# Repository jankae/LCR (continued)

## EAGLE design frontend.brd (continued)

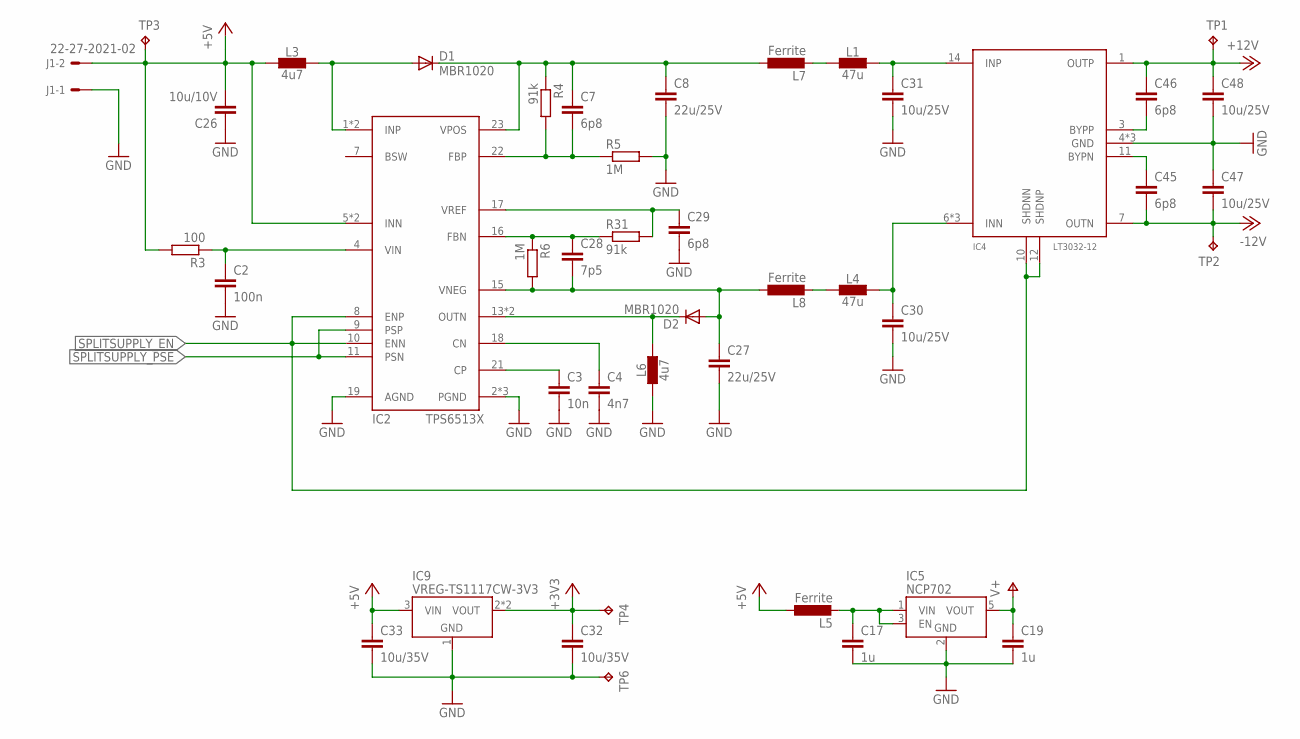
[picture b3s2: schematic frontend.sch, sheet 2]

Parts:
C2: 100n; C0603K
C3: 10n; C0603K
C4: 4n7; C0603K
C7, C29, C45, C46: 6p8; C0603K
C8, C27: 22u/25V; C1206K
C17, C19: 1u; C0603
C26: 10u/10V; C1206K
C28: 7p5; C0603K
C30, C31, C47, C48: 10u/25V; C1206K
C32, C33: 10u/35V; C1206K
D1, D2: MBR1020; SOD123
IC2: TPS6513X; QFN50P400X400X100-25T250N
IC4: LT3032-12; SON50P300X400X80-14N
IC5: NCP702; SOT95P240X110-5
IC9: VREG-TS1117CW-3V3; SOT223
J1: 22-27-2021-02; 6410-02
L1, L4: 47u; L_1212
L3, L6: 4u7; L_1212
L5, L7, L8: Ferrite; R0603
R3: 100; R0603
R4, R31: 91k; R0603
R5, R6: 1M; R0603
TP1, TP2, TP3, TP4, TP6: TPB2,54; B2,54

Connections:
+3V3: C32.1, IC9.2 (VOUT), IC9.4 (VOUT), TP4.TP; also elsewhere on the board
+5V: C26.2, C33.1, IC2.5 (INN), IC2.6 (INN), IC9.3 (VIN), J1.2, L3.1, L5.1, R3.2, TP3.TP; also elsewhere on the board
+12V: C46.1, C48.1, IC4.1 (OUTP), TP1.TP; also elsewhere on the board
-12V: C45.2, C47.2, IC4.7 (OUTN), TP2.TP; also elsewhere on the board
GND: C2.2, C3.2, C4.2, C8.2, C17.2, C19.2, C26.1, C27.2, C29.2, C30.2, C31.2, C32.2, C33.2, C47.1, C48.2, IC2.2 (PGND), IC2.3 (PGND), IC2.19 (AGND), IC2.25 (PGND), IC4.4 (GND), IC4.5 (GND), IC4.EP4 (GND), IC5.2 (GND), IC9.1 (GND), J1.1, L6.1, R5.2, TP6.TP; also elsewhere on the board
unnamed: C17.1, IC5.1 (VIN), IC5.3 (EN), L5.2
unnamed: C2.1, IC2.4 (VIN), R3.1
unnamed: D1.A, IC2.1 (INP), IC2.24 (INP), L3.2
unnamed: C7.1, C8.1, D1.C, IC2.23 (VPOS), L7.1, R4.1
unnamed: D2.C, IC2.13 (OUTN), IC2.14 (OUTN), L6.2
unnamed: C3.1, IC2.21 (CP)
unnamed: C4.1, IC2.18 (CN)
unnamed: C7.2, IC2.22 (FBP), R4.2, R5.1
unnamed: C27.1, C28.2, D2.A, IC2.15 (VNEG), L8.1, R6.2
unnamed: L4.1, L8.2
unnamed: C30.1, IC4.6 (INN), IC4.9 (INN), IC4.EP9 (INN), L4.2
unnamed: C29.1, IC2.17 (VREF), R31.2
unnamed: C28.1, IC2.16 (FBN), R6.1, R31.1
unnamed: L1.1, L7.2
unnamed: C31.1, IC4.14 (INP), L1.2
unnamed: C46.2, IC4.3 (BYPP)
unnamed: C45.1, IC4.11 (BYPN)
SPLITSUPPLY_EN: IC2.8 (ENP), IC2.10 (ENN), IC4.10 (SHDNN), IC4.12 (SHDNP)
SPLITSUPPLY_PSE: IC2.9 (PSP), IC2.11 (PSN)
V+: C19.1, IC5.5 (VOUT); also elsewhere on the board

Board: 4 copper layers, 114 parts (4 on the bottom side), 85 nets, no tracks yet.

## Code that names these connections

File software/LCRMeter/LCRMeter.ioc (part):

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Mcu.Name=STM32F303V(D-E)Tx
Mcu.Package=LQFP100
Mcu.UserName=STM32F303VETx
PA0.GPIOParameters=GPIO_Label
PA0.GPIO_Label=TOUCH_IRQ
PA0.Signal=GPIO_Input
PA1.GPIOParameters=GPIO_Speed,PinState,GPIO_Label
PA1.GPIO_Label=DISP_CS
PA1.GPIO_Speed=GPIO_SPEED_FREQ_HIGH
PA1.PinState=GPIO_PIN_SET
PA1.Signal=GPIO_Output
PA10.Mode=Asynchronous
PA10.Signal=USART1_RX
PA11.Mode=Device
PA11.Signal=USB_DM
PA12.Mode=Device
PA12.Signal=USB_DP
PA13.Mode=Serial_Wire
PA13.Signal=SYS_JTMS-SWDIO
PA14.Mode=Serial_Wire
PA14.Signal=SYS_JTCK-SWCLK
PA2.GPIOParameters=GPIO_Speed,GPIO_Label
PA2.GPIO_Label=DISP_RST
PA2.GPIO_Speed=GPIO_SPEED_FREQ_HIGH
PA2.Signal=GPIO_Output
PA3.GPIOParameters=GPIO_Speed,PinState,GPIO_Label
PA3.GPIO_Label=SD_CS
PA3.GPIO_Speed=GPIO_SPEED_FREQ_HIGH
PA3.PinState=GPIO_PIN_SET
PA3.Signal=GPIO_Output
PA5.Mode=Full_Duplex_Master
PA5.Signal=SPI1_SCK
PA6.Mode=Full_Duplex_Master
PA6.Signal=SPI1_MISO
PA7.Mode=Full_Duplex_Master
PA7.Signal=SPI1_MOSI
PA8.GPIOParameters=GPIO_Speed,GPIO_Label
PA8.GPIO_Label=USB_IDENT
PA8.GPIO_Speed=GPIO_SPEED_FREQ_LOW
PA8.Signal=GPIO_Output
PA9.Mode=Asynchronous
PA9.Signal=USART1_TX
PB3.Mode=Full_Duplex_Master
PB3.Signal=SPI3_SCK
PB4.Mode=Full_Duplex_Master
PB4.Signal=SPI3_MISO
PB5.Mode=Full_Duplex_Master
PB5.Signal=SPI3_MOSI
PB6.GPIOParameters=GPIO_Speed,PinState,GPIO_Label
PB6.GPIO_Label=AD5941_CS
PB6.GPIO_Speed=GPIO_SPEED_FREQ_HIGH
PB6.PinState=GPIO_PIN_SET
PB6.Signal=GPIO_Output
PB7.GPIOParameters=GPIO_Speed,GPIO_Label
PB7.GPIO_Label=AD5941_RESET
PB7.GPIO_Speed=GPIO_SPEED_FREQ_LOW
PB7.Signal=GPIO_Output
PB8.GPIOParameters=GPIO_Label
PB8.GPIO_Label=SOUND_INT
PB8.Signal=S_TIM8_CH2
PC13.GPIOParameters=GPIO_Speed,GPIO_Label
PC13.GPIO_Label=DISP_RS
PC13.GPIO_Speed=GPIO_SPEED_FREQ_LOW
PC13.Signal=GPIO_Output
PC14-OSC32_IN.GPIOParameters=GPIO_Speed,GPIO_Label
PC14-OSC32_IN.GPIO_Label=DISP_WR
PC14-OSC32_IN.GPIO_Speed=GPIO_SPEED_FREQ_LOW
PC14-OSC32_IN.Signal=GPIO_Output
PC15-OSC32_OUT.GPIOParameters=GPIO_Speed,GPIO_Label
PC15-OSC32_OUT.GPIO_Label=DISP_RD
PC15-OSC32_OUT.GPIO_Speed=GPIO_SPEED_FREQ_LOW
PC15-OSC32_OUT.Signal=GPIO_Output
PE0.GPIOParameters=GPIO_Speed,GPIO_Label
PE0.GPIO_Label=DISP_IO0
PE0.GPIO_Speed=GPIO_SPEED_FREQ_HIGH
PE0.Signal=GPIO_Output
PE1.GPIOParameters=GPIO_Speed,GPIO_Label
PE1.GPIO_Label=DISP_IO1
PE1.GPIO_Speed=GPIO_SPEED_FREQ_HIGH
PE1.Signal=GPIO_Output
PE10.GPIOParameters=GPIO_Speed,GPIO_Label
PE10.GPIO_Label=DISP_IO10
PE10.GPIO_Speed=GPIO_SPEED_FREQ_HIGH
PE10.Signal=GPIO_Output
PE11.GPIOParameters=GPIO_Speed,GPIO_Label
PE11.GPIO_Label=DISP_IO11
PE11.GPIO_Speed=GPIO_SPEED_FREQ_HIGH
PE11.Signal=GPIO_Output
PE12.GPIOParameters=GPIO_Speed,GPIO_Label
PE12.GPIO_Label=DISP_IO12
PE12.GPIO_Speed=GPIO_SPEED_FREQ_HIGH
PE12.Signal=GPIO_Output
PE13.GPIOParameters=GPIO_Speed,GPIO_Label
PE13.GPIO_Label=DISP_IO13
PE13.GPIO_Speed=GPIO_SPEED_FREQ_HIGH
PE13.Signal=GPIO_Output
PE14.GPIOParameters=GPIO_Speed,GPIO_Label
PE14.GPIO_Label=DISP_IO14
PE14.GPIO_Speed=GPIO_SPEED_FREQ_HIGH
PE14.Signal=GPIO_Output
PE15.GPIOParameters=GPIO_Speed,GPIO_Label
PE15.GPIO_Label=DISP_IO15
PE15.GPIO_Speed=GPIO_SPEED_FREQ_HIGH
PE15.Signal=GPIO_Output
PE2.GPIOParameters=GPIO_Speed,GPIO_Label
PE2.GPIO_Label=DISP_IO2
PE2.GPIO_Speed=GPIO_SPEED_FREQ_HIGH
PE2.Signal=GPIO_Output
PE3.GPIOParameters=GPIO_Speed,GPIO_Label
PE3.GPIO_Label=DISP_IO3
PE3.GPIO_Speed=GPIO_SPEED_FREQ_HIGH
PE3.Signal=GPIO_Output
PE4.GPIOParameters=GPIO_Speed,GPIO_Label
PE4.GPIO_Label=DISP_IO4
PE4.GPIO_Speed=GPIO_SPEED_FREQ_HIGH
PE4.Signal=GPIO_Output
PE5.GPIOParameters=GPIO_Speed,GPIO_Label
PE5.GPIO_Label=DISP_IO5
PE5.GPIO_Speed=GPIO_SPEED_FREQ_HIGH
PE5.Signal=GPIO_Output
PE6.GPIOParameters=GPIO_Speed,GPIO_Label
PE6.GPIO_Label=DISP_IO6
PE6.GPIO_Speed=GPIO_SPEED_FREQ_HIGH
PE6.Signal=GPIO_Output
PE7.GPIOParameters=GPIO_Speed,GPIO_Label
PE7.GPIO_Label=DISP_IO7
PE7.GPIO_Speed=GPIO_SPEED_FREQ_HIGH
PE7.Signal=GPIO_Output
PE8.GPIOParameters=GPIO_Speed,GPIO_Label
PE8.GPIO_Label=DISP_IO8
PE8.GPIO_Speed=GPIO_SPEED_FREQ_HIGH
PE8.Signal=GPIO_Output
PE9.GPIOParameters=GPIO_Speed,GPIO_Label
PE9.GPIO_Label=DISP_IO9
PE9.GPIO_Speed=GPIO_SPEED_FREQ_HIGH
PE9.Signal=GPIO_Output
PF0-OSC_IN.Mode=HSE-External-Oscillator
PF0-OSC_IN.Signal=RCC_OSC_IN
PF1-OSC_OUT.Mode=HSE-External-Oscillator
PF1-OSC_OUT.Signal=RCC_OSC_OUT
PF9.GPIOParameters=GPIO_Speed,PinState,GPIO_Label
PF9.GPIO_Label=TOUCH_CS
PF9.GPIO_Speed=GPIO_SPEED_FREQ_HIGH
PF9.PinState=GPIO_PIN_SET
PF9.Signal=GPIO_Output
RCC.HSE_VALUE=16000000
RCC.SYSCLKFreq_VALUE=72000000
RCC.SYSCLKSourceVirtual=RCC_SYSCLKSOURCE_PLLCLK
board=custom

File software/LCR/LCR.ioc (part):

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Mcu.Name=STM32F303V(B-C)Tx
Mcu.Package=LQFP100
Mcu.UserName=STM32F303VCTx
PA0.GPIOParameters=GPIO_PuPd,GPIO_Label,GPIO_Mode
PA0.GPIO_Label=B1 [Blue PushButton]
PA0.GPIO_Mode=GPIO_MODE_INPUT
PA0.GPIO_PuPd=GPIO_NOPULL
PA0.Signal=GPIO_Input
PA1.Mode=IN2-Differential
PA1.Signal=ADC1_IN2
PA11.GPIOParameters=GPIO_Label
PA11.GPIO_Label=DM
PA11.Signal=USB_DM
PA12.GPIOParameters=GPIO_Label
PA12.GPIO_Label=DP
PA12.Signal=USB_DP
PA13.GPIOParameters=GPIO_Label
PA13.GPIO_Label=SWDIO
PA13.Signal=SYS_JTMS-SWDIO
PA14.GPIOParameters=GPIO_Label
PA14.GPIO_Label=SWCLK
PA14.Signal=SYS_JTCK-SWCLK
PA2.Mode=IN2-Differential
PA2.Signal=ADC1_IN3
PA4.Signal=COMP_DAC1_group
PA5.GPIOParameters=GPIO_Speed,GPIO_PuPd,GPIO_Label,GPIO_Mode
PA5.GPIO_Label=SPI1_SCK [L3GD20_SCL/SPC]
PA5.GPIO_Mode=GPIO_MODE_AF_PP
PA5.GPIO_PuPd=GPIO_NOPULL
PA5.GPIO_Speed=GPIO_SPEED_FREQ_LOW
PA5.Signal=SPI1_SCK
PA6.GPIOParameters=GPIO_Speed,GPIO_PuPd,GPIO_Label,GPIO_Mode
PA6.GPIO_Label=SPI1_MISO [L3GD20_SA0/SDO]
PA6.GPIO_Mode=GPIO_MODE_AF_PP
PA6.GPIO_PuPd=GPIO_NOPULL
PA6.GPIO_Speed=GPIO_SPEED_FREQ_LOW
PA6.Signal=SPI1_MISO
PA7.GPIOParameters=GPIO_Speed,GPIO_PuPd,GPIO_Label,GPIO_Mode
PA7.GPIO_Label=SPI1_MISO [L3GD20_SDA/SDI/SDO]
PA7.GPIO_Mode=GPIO_MODE_AF_PP
PA7.GPIO_PuPd=GPIO_NOPULL
PA7.GPIO_Speed=GPIO_SPEED_FREQ_LOW
PA7.Signal=SPI1_MOSI
PB12.Signal=SPI2_NSS
PB13.Mode=Full_Duplex_Master
PB13.Signal=SPI2_SCK
PB14.Mode=Full_Duplex_Master
PB14.Signal=SPI2_MISO
PB15.Mode=Full_Duplex_Master
PB15.Signal=SPI2_MOSI
PB3.GPIOParameters=GPIO_Label
PB3.GPIO_Label=SWO
PB3.Signal=SYS_JTDO-TRACESWO
PB6.GPIOParameters=GPIO_FM6,GPIO_Speed,GPIO_PuPd,GPIO_Label,GPIO_Mode
PB6.GPIO_FM6=__NULL
PB6.GPIO_Label=I2C1_SCL [LSM303DLHC_SCL]
PB6.GPIO_Mode=GPIO_MODE_AF_OD
PB6.GPIO_PuPd=GPIO_NOPULL
PB6.GPIO_Speed=GPIO_SPEED_FREQ_LOW
PB6.Signal=I2C1_SCL
PB7.GPIOParameters=GPIO_Speed,GPIO_PuPd,GPIO_Label,GPIO_FM7,GPIO_Mode
PB7.GPIO_FM7=__NULL
PB7.GPIO_Label=I2C1_SDA [LSM303DLHC_SDA]
PB7.GPIO_Mode=GPIO_MODE_AF_OD
PB7.GPIO_PuPd=GPIO_NOPULL
PB7.GPIO_Speed=GPIO_SPEED_FREQ_LOW
PB7.Signal=I2C1_SDA
PC14-OSC32_IN.GPIOParameters=GPIO_Label
PC14-OSC32_IN.GPIO_Label=OSC32_IN
PC14-OSC32_IN.Signal=RCC_OSC32_IN
PC15-OSC32_OUT.GPIOParameters=GPIO_Label
PC15-OSC32_OUT.GPIO_Label=OSC32_OUT
PC15-OSC32_OUT.Signal=RCC_OSC32_OUT
PC4.Mode=Asynchronous
PC4.Signal=USART1_TX
PC5.Mode=Asynchronous
PC5.Signal=USART1_RX
PE0.GPIOParameters=GPIO_PuPd,GPIO_Label,GPIO_ModeDefaultEXTI
PE0.GPIO_Label=MEMS_INT1 [L3GD20_INT1]
PE0.GPIO_ModeDefaultEXTI=GPIO_MODE_EVT_RISING
PE0.GPIO_PuPd=GPIO_NOPULL
PE0.Signal=GPXTI0
PE1.GPIOParameters=GPIO_PuPd,GPIO_Label,GPIO_ModeDefaultEXTI
PE1.GPIO_Label=MEMS_INT2 [L3GD20_DRDY/INT2]
PE1.GPIO_ModeDefaultEXTI=GPIO_MODE_EVT_RISING
PE1.GPIO_PuPd=GPIO_NOPULL
PE1.Signal=GPXTI1
PE10.GPIOParameters=GPIO_Speed,GPIO_PuPd,GPIO_Label,GPIO_ModeDefaultOutputPP
PE10.GPIO_Label=LD5 [Orange Led]
PE10.GPIO_ModeDefaultOutputPP=GPIO_MODE_OUTPUT_PP
PE10.GPIO_PuPd=GPIO_NOPULL
PE10.GPIO_Speed=GPIO_SPEED_FREQ_LOW
PE10.Signal=GPIO_Output
PE11.GPIOParameters=GPIO_Speed,GPIO_PuPd,GPIO_Label,GPIO_ModeDefaultOutputPP
PE11.GPIO_Label=LD7 [Green Led]
PE11.GPIO_ModeDefaultOutputPP=GPIO_MODE_OUTPUT_PP
PE11.GPIO_PuPd=GPIO_NOPULL
PE11.GPIO_Speed=GPIO_SPEED_FREQ_LOW
PE11.Signal=GPIO_Output
PE12.GPIOParameters=GPIO_Speed,GPIO_PuPd,GPIO_Label,GPIO_ModeDefaultOutputPP
PE12.GPIO_Label=LD9 [Blue Led]
PE12.GPIO_ModeDefaultOutputPP=GPIO_MODE_OUTPUT_PP
PE12.GPIO_PuPd=GPIO_NOPULL
PE12.GPIO_Speed=GPIO_SPEED_FREQ_LOW
PE12.Signal=GPIO_Output
PE13.GPIOParameters=GPIO_Speed,GPIO_PuPd,GPIO_Label,GPIO_ModeDefaultOutputPP
PE13.GPIO_Label=LD10 [Red Led]
PE13.GPIO_ModeDefaultOutputPP=GPIO_MODE_OUTPUT_PP
PE13.GPIO_PuPd=GPIO_NOPULL
PE13.GPIO_Speed=GPIO_SPEED_FREQ_LOW
PE13.Signal=GPIO_Output
PE14.GPIOParameters=GPIO_Speed,GPIO_PuPd,GPIO_Label,GPIO_ModeDefaultOutputPP
PE14.GPIO_Label=LD8 [Orange Led]
PE14.GPIO_ModeDefaultOutputPP=GPIO_MODE_OUTPUT_PP
PE14.GPIO_PuPd=GPIO_NOPULL
PE14.GPIO_Speed=GPIO_SPEED_FREQ_LOW
PE14.Signal=GPIO_Output
PE15.GPIOParameters=GPIO_Speed,GPIO_PuPd,GPIO_Label,GPIO_ModeDefaultOutputPP
PE15.GPIO_Label=LD6 [Green Led]
PE15.GPIO_ModeDefaultOutputPP=GPIO_MODE_OUTPUT_PP
PE15.GPIO_PuPd=GPIO_NOPULL
PE15.GPIO_Speed=GPIO_SPEED_FREQ_LOW
PE15.Signal=GPIO_Output
PE2.GPIOParameters=GPIO_PuPd,GPIO_Label,GPIO_ModeDefaultEXTI
PE2.GPIO_Label=DRDY [LSM303DLHC_DRDY]
PE2.GPIO_ModeDefaultEXTI=GPIO_MODE_EVT_RISING
PE2.GPIO_PuPd=GPIO_NOPULL
PE2.Signal=GPXTI2
PE3.GPIOParameters=GPIO_Speed,GPIO_PuPd,GPIO_Label,GPIO_ModeDefaultOutputPP
PE3.GPIO_Label=CS_I2C/SPI [L3GD20_CS_I2C/SPI]
PE3.GPIO_ModeDefaultOutputPP=GPIO_MODE_OUTPUT_PP
PE3.GPIO_PuPd=GPIO_NOPULL
PE3.GPIO_Speed=GPIO_SPEED_FREQ_LOW
PE3.Signal=GPIO_Output
PE4.GPIOParameters=GPIO_PuPd,GPIO_Label,GPIO_ModeDefaultEXTI
PE4.GPIO_Label=MEMS_INT3 [LSM303DLHC_INT1]
PE4.GPIO_ModeDefaultEXTI=GPIO_MODE_EVT_RISING
PE4.GPIO_PuPd=GPIO_NOPULL
PE4.Signal=GPXTI4
PE5.GPIOParameters=GPIO_PuPd,GPIO_Label,GPIO_ModeDefaultEXTI
PE5.GPIO_Label=MEMS_INT4 [LSM303DLHC_INT2]
PE5.GPIO_ModeDefaultEXTI=GPIO_MODE_EVT_RISING
PE5.GPIO_PuPd=GPIO_NOPULL
PE5.Signal=GPXTI5
PE8.GPIOParameters=GPIO_Speed,GPIO_PuPd,GPIO_Label,GPIO_ModeDefaultOutputPP
PE8.GPIO_Label=LD4 [Blue Led]
PE8.GPIO_ModeDefaultOutputPP=GPIO_MODE_OUTPUT_PP
PE8.GPIO_PuPd=GPIO_NOPULL
PE8.GPIO_Speed=GPIO_SPEED_FREQ_LOW
PE8.Signal=GPIO_Output
PE9.GPIOParameters=GPIO_Speed,GPIO_PuPd,GPIO_Label,GPIO_ModeDefaultOutputPP
PE9.GPIO_Label=LD3 [Red Led]
PE9.GPIO_ModeDefaultOutputPP=GPIO_MODE_OUTPUT_PP
PE9.GPIO_PuPd=GPIO_NOPULL
PE9.GPIO_Speed=GPIO_SPEED_FREQ_LOW
PE9.Signal=GPIO_Output
PF0-OSC_IN.GPIOParameters=GPIO_Label
PF0-OSC_IN.GPIO_Label=OSC_IN
PF0-OSC_IN.Mode=HSE-External-Oscillator
PF0-OSC_IN.Signal=RCC_OSC_IN
PF1-OSC_OUT.GPIOParameters=GPIO_Label
PF1-OSC_OUT.GPIO_Label=OSC_OUT
PF1-OSC_OUT.Mode=HSE-External-Oscillator
PF1-OSC_OUT.Signal=RCC_OSC_OUT
PF10.GPIOParameters=GPIO_Label
PF10.GPIO_Label=TRIGGER
PF10.Signal=GPIO_Output
RCC.HSEPLLFreq_Value=8000000
RCC.HSE_VALUE=8000000
RCC.SYSCLKFreq_VALUE=72000000
RCC.SYSCLKSourceVirtual=RCC_SYSCLKSOURCE_PLLCLK
board=STM32F3DISCOVERY
boardIOC=true

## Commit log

2019-01-19 Software for breadboard test
2020-03-08 Beginning of new design based on AD5941
2020-03-13 Cleanup of old HW/code and created OS structure + GUI code
2020-03-19 GUI improvements from Signalgenerator merged
2020-03-26 Bugfixes Display and touch driver
2020-03-27 Bugfixes AD5941 clock system and excitation signal generation
2020-03-28 Autoranging, ADC overload detection, excitation amplitude corrected
2020-03-29 Low/high frequency settings fixed, acquisition bar and faster autoranging
2020-03-29 Min/max impedance display, Sound
2020-04-04 Basic sweep functionality
2020-04-05 Sweep with menu instead of popup window, improved sweep graph display redraw
2020-04-05 Auto model mode changed, log/lin indicator on sweep axis
2020-04-05 open/short lead compensation
2020-04-07 Marker readout in sweep, sweep acquition fix when wrapping around
2020-04-07 Pictures
2024-02-19 Replacement pmf_cast with a standard C++11 solution: std::function and lambdas
2024-02-19 Fix warning/error: incompatible implicit declaration of built-in function 'strchr' (a value of type "int" cannot be assigned to an entity of type "char const *")
2024-02-19 Replace __builtin_clz with __CLZ (CMSIS standard)
2024-02-19 Variable length arrays (VLAs) is not C++11 standard but C99
2024-02-19 Define M_PI and M_SQRT1_2 if not defined
2024-02-19 Correct __BKPT value
2024-02-19 Fix warning/error: invalid conversion from 'Widget*' to 'MenuEntry*' (a value of type "Widget *" cannot be used to initialize an entity of type "MenuEntry *")
2024-02-19 Fix warning/error: invalid conversion from 'uint32_t* {aka long unsigned int*}' to 'long int*' (no instance of constructor "MenuValue<T>::MenuValue [with T=int32_t]" matches the argument list)
2024-02-19 Fix warning/error: more than one instance of overloaded function "abs" matches the argument list
2024-02-19 To avoid possible linker errors, a C99 inline function should additionally be static or external
2024-02-19 Own HardFault_Handler for each compiler
2024-02-19 Correct calibration resistor value. Thanks to wocard2
2024-02-19 Correct Vbias0 of AD5941. Thanks to wocard2
2024-02-19 Correct typical value for the Internal reference voltage of the STM32F303. Thanks to wocard2
2024-02-19 Add support for XPT2046 touch controller
2024-02-20 Change debug options
2024-02-20 Add IAR project
2024-02-20 Add a modified version of the circuit and PCB
2024-02-20 Add laser-cut acrylic case design
2024-02-20 Add new pictures
2024-02-20 Add to README.md
